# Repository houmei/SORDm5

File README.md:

# SORD m5 project
## SORDM5C - Cartridge board for SORD m5
## SORDM5PSA - Power Supply

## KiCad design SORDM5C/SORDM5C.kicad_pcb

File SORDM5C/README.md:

# SORDM5C - Cartridge board for SORD m5 (KiCad5)

Schematic

PCB

## 説明

[SORDm5C V01L02 SORD m5用ROM/RAMカートリッジ](http://blog.livedoor.jp/hardyboy/archives/10058478.html "まごころせいじつ堂")  
[SORD m5用ROM/RAMカートリッジ基板](https://keisanki.booth.pm/items/3939000 "booth")  
・C4 470pFは不要です(元々のカートリッジでは~MRD信号を遅らせるために付いていたがU3で確保できている)  
・カードエッジ端面はやすりなどで角を面取りしてください。  

## 履歴
V01L01(非公開) 初版 ROMデコードの配線ミスあり  
V01L02(非公開) V01L01のデコード修正　リセットボタン追加  
V01L03 リセットボタンの形状変更　カードエッジの位置をずらしケースとの干渉を改善　回路図はV01L02と変わらず    

## SORDM5CV01L03GB - Gerber
JLCPCBなどにそのまま出図可能です。

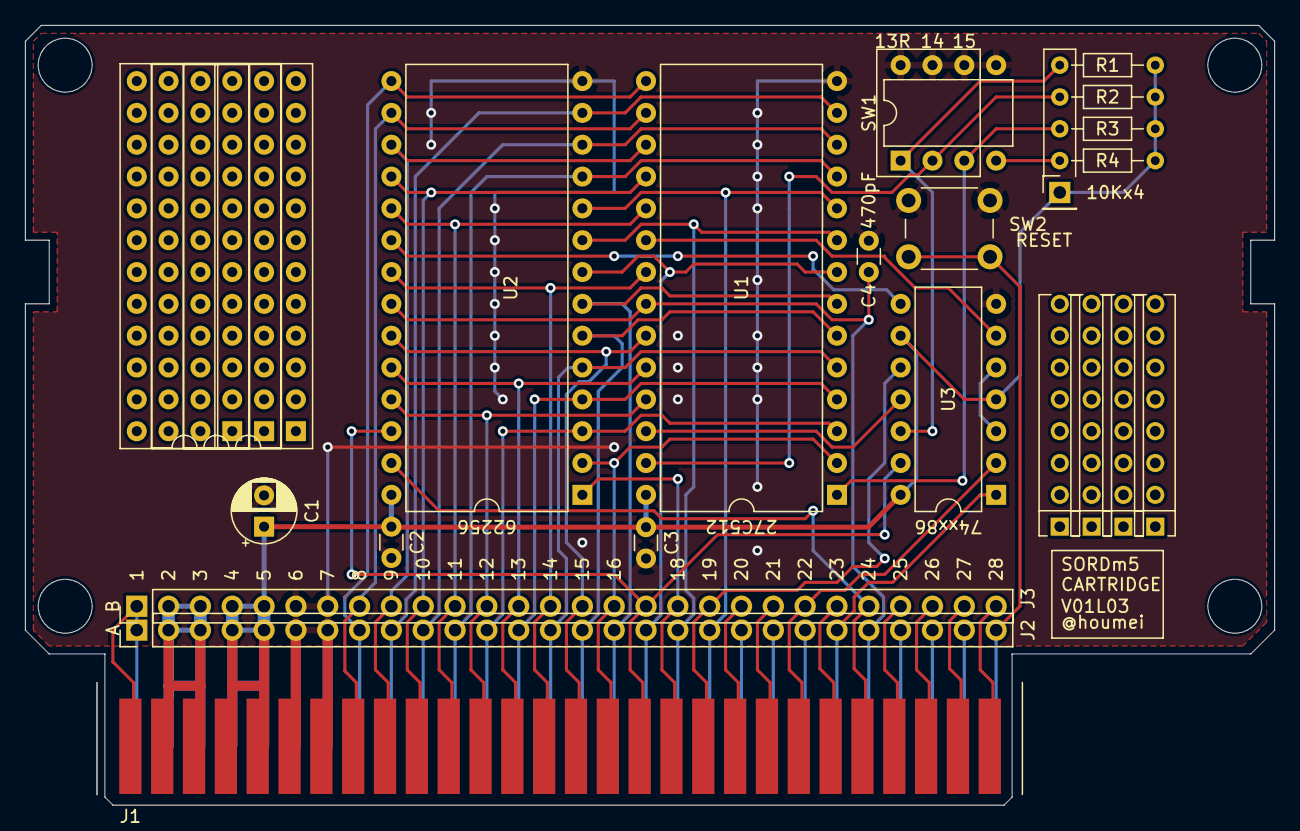
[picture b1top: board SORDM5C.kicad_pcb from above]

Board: 2 copper layers, 99.7 x 62.2 mm, 17 parts (0 on the bottom side), 54 nets.

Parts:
C1: 3.3uF; CP_Radial_D5.0mm_P2.50mm
C2, C3: 0.1uF; C_Disc_D3.0mm_W1.6mm_P2.50mm
C4: 470pF; C_Disc_D3.0mm_W1.6mm_P2.50mm
J1: Conn_02x28_Top_Bottom; SORDm5_CARTRIDGE_28P
J2, J3: Conn_01x28; PinHeader_1x28_P2.54mm_Vertical
J4: Conn_01x01_Male; PinHeader_1x01_P2.54mm_Vertical
R1, R2, R3, R4: 10K; R_Axial_DIN0204_L3.6mm_D1.6mm_P7.62mm_Horizontal
SW1: SW_DIP_x04; DIP-8_W7.62mm
SW2: SW_Push; SW_PUSH_6mm
U1: 27C512; DIP-28_W15.24mm
U2: HM62256BLP; DIP-28_W15.24mm
U3: 74HC86; DIP-14_W7.62mm

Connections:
+5V: C1.1, C2.1, C3.1, J1.4, J1.5, J1.32, J1.33, J2.4, J2.5, J3.4, J3.5, J4.1, R1.1, R2.1, R3.1, R4.1, U1.28, U2.28, U3.4, U3.9, U3.14
+12V: J1.2, J1.3, J1.30, J1.31, J2.2, J2.3, J3.2, J3.3
-12V: J1.1, J1.29, J2.1, J3.1
A0: J1.19, J2.19, U1.10, U2.10
A1: J1.18, J2.18, U1.9, U2.9
A2: J1.17, J2.17, U1.8, U2.8
A3: J1.16, J2.16, U1.7, U2.7
A4: J1.15, J2.15, U1.6, U2.6
A5: J1.14, J2.14, U1.5, U2.5
A6: J1.13, J2.13, U1.4, U2.4
A7: J1.12, J2.12, U1.3, U2.3
A8: J1.40, J3.12, U1.25, U2.25
A9: J1.41, J3.13, U1.24, U2.24
A10: J1.42, J3.14, U1.21, U2.21
A11: J1.43, J3.15, U1.23, U2.23
A12: J1.44, J3.16, U1.2, U2.2
A13: J1.45, J3.17, U2.26, U3.13
A13R: R1.2, SW1.1, U3.12
A14: J1.46, J3.18, U2.1
A14SEL: R2.2, SW1.2, U1.27
A15: J1.47, J3.19, U3.10
A15SEL: R3.2, SW1.3, U1.1
D0: J1.11, J2.11, U1.11, U2.11
D1: J1.10, J2.10, U1.12, U2.12
D2: J1.9, J2.9, U1.13, U2.13
D3: J1.8, J2.8, U1.15, U2.15
D4: J1.36, J3.8, U1.16, U2.16
D5: J1.37, J3.9, U1.17, U2.17
D6: J1.38, J3.10, U1.18, U2.18
D7: J1.39, J3.11, U1.19, U2.19
EXCLK: J1.55, J3.27
GND: C1.2, C2.2, C3.2, C4.2, J1.6, J1.7, J1.34, J1.35, J2.6, J2.7, J3.6, J3.7, SW1.5, SW1.6, SW1.7, SW1.8, SW2.1, U1.14, U2.14, U3.7
unnamed: R4.2, SW1.4
unnamed: U1.20, U3.6
unnamed: U1.26, U3.11
unnamed: U2.20, U3.8
unnamed: U3.3, U3.5
PHI: J1.56, J3.28
~EXINT: J1.27, J2.27
~EXIOA: J1.26, J2.26
~EXIOB: J1.54, J3.26
~EXM: J1.51, J3.23
~IORD: J1.25, J2.25
~IOWR: J1.53, J3.25
~MRD: C4.1, J1.24, J2.24, U1.22, U2.22
~MRQ: J1.48, J3.20
~MWR: J1.52, J3.24, U2.27
~RFSH: J1.49, J3.21
~ROM0: J1.22, J2.22
~ROM1: J1.50, J3.22, U3.2
~ROM2: J1.23, J2.23, U3.1
~ROMDS: J1.21, J2.21
~RST: J1.28, J2.28, SW2.2
~WAIT: J1.20, J2.20
